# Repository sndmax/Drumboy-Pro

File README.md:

# Drumboy Pro

📖 **[Developer Wiki](https://www.randomwaves.io/drumboy-pro/drumboy-pro-wiki.html)** — full hardware specs, schematics walkthrough, firmware architecture, DSP internals, and memory map.

**An open-source hardware groovebox** — sequencer, sampler, and DSP effects engine built around an STM32H723 (Cortex-M7 @ 550 MHz), with a 540×960 touch-free color display, 42 keys, 8 rotary encoders, and full MIDI/Sync I/O.

This repository holds the complete hardware design (KiCad) and firmware (STM32CubeIDE / C++) for Drumboy Pro, released by [Randomwaves](https://randomwaves.io) as an open hardware/software project.

---

## Overview

The MCU sits at the center of six subsystems: an NT35510 display driven over a 16-bit parallel GPIO bus, 16 MB of external SDRAM for sample streaming, an SGTL5000 audio codec over I2S/I2C, a microSD card for storage, a control surface fanned out over six MCP23017 I/O expanders, and external connectivity (MIDI, Sync, USB-C power).

| | |
|---|---|
| **MCU** | STM32H723ZGT6 — Cortex-M7 @ 550 MHz (VOS0), LQFP-144 |
| **Display** | NT35510, 540×960, 16-bit parallel |
| **SDRAM** | 16 MB (IS42S16800J-7TL-TR), FMC bus |
| **Audio codec** | SGTL5000 — I2S3 audio / I2C3 control |
| **Storage** | microSD (TF-01A), SDMMC2, FAT filesystem |
| **Control surface** | 42 keys, 42 LEDs, 8 rotary encoders — 6× MCP23017 over I2C |
| **Connectivity** | MIDI In/Out, Sync In/Out, USB-C power |
| **Flash** | 1024 KB, split between bootloader and application |

## Features

- **10 sample layers**, each independently modulated by a 10-slot LFO matrix (sample-and-hold at note-trigger time)
- **Per-layer routing** into a shared DSP chain: parametric EQ → 2× multimode filter → 2× send effect → stereo reverb
- **9 effect types** per send slot: Delay, Chorus, Flanger, Phaser, Compressor, Expander, Overdrive, Distortion, Bitcrusher
- **Freeverb/Schroeder-Moorer style reverb** with pre-delay, stereo surround derivation, and nine built-in profiles: Default, Tight, Snap, Chamber, Warehouse, Disco, Dub, Ghost, Texture
- **Sequencer** with 5 song banks per layer, 64 beats per bank, and algorithmic complex-fill generation (timing alignment × level curve templates)
- Hold **Copy** while increasing **Bars** to double the bar count (for example, 2 → 4) and duplicate the entire current song bank across all instruments. Doubling must fit the song-length limit; each bank supports 64 beats and 32 complex fills.
- **MIDI In/Out** (opto-isolated input) and **Sync In/Out** for external clock/gate sync
- **SD-card firmware updates** via a dedicated bootloader with CRC-32 verified staged writes
- Fully open hardware (KiCad) and firmware (C/C++ against the STM32 HAL) — no CMSIS-DSP or external DSP library, all hand-rolled biquad/delay-line DSP on the Cortex-M7 FPU

Choose **Profile** with the second encoder in the Reverb menu or select the field with left/right and change it with up/down. Each profile enables reverb and applies its complete settings through a bypass transition. **Tight** is the starting profile at initialization and for new projects and drumkits. **Default** retains the original settings for an explicit reverb reset and recovery from invalid saved parameters.

| Profile | Intended use | Size | Decay | Damping | PreDelay (ms) | Surround (%) | Dry | Wet |
|---|---|---:|---:|---:|---:|---:|---:|---:|
| Default | Original reset settings | 25 | 50 | 30 | 5 | 25 | 100 | 50 |
| Tight | Techno/house grooves, hats and shakers | 25 | 32 | 65 | 8 | 25 | 100 | 18 |
| Snap | Breakbeat, fast snare/clap and percussion | 10 | 15 | 40 | 10 | 10 | 100 | 18 |
| Chamber | Dark hypnotic percussion, rims and toms | 38 | 55 | 70 | 3 | 30 | 100 | 25 |
| Warehouse | Sparse hits, rides and transitions | 68 | 40 | 60 | 20 | 40 | 100 | 25 |
| Disco | Brighter house/Italo claps, snares and stabs | 40 | 50 | 25 | 20 | 30 | 100 | 30 |
| Dub | Leftfield accents and delay into reverb | 52 | 70 | 75 | 30 | 40 | 100 | 35 |
| Ghost | Wet textures with a shorter tail | 72 | 80 | 70 | 4 | 65 | 0 | 100 |
| Texture | Long atmospheric tails and transitions | 100 | 100 | 65 | 40 | 80 | 0 | 100 |

**Ghost** and **Texture** use Dry 0% / Wet 100% on the shared reverb bus: every source routed into reverb loses its direct signal. For a dedicated texture, route only the intended sources into that bus. Manual edits display **Custom** unless all settings match a built-in profile; the global Size encoder assignment remains available. Projects and drumkits keep the existing file format and restore the profile name from the saved settings. Older Room, Hall, Dark and Ambient settings load as Custom with their parameters preserved.

## Repository structure

```
01 Hardware/
  Main/       KiCad project — main board (Drumboy_Main)
  Top/        KiCad project — top/control-surface board (Drumboy_Top)
  Drawing/    Mechanical drawings, enclosure models, graphics, fonts

02 Software/
  Drumboy-Pro-Boot-H723/   Bootloader — STM32CubeIDE project (own repo, linked below)
  Drumboy-Pro-App-H723/    Application firmware — STM32CubeIDE project (own repo, linked below)
  Firmware/                 Prebuilt firmware binaries
  Sd Card/                  Reference SD card contents (samples, presets, drumkits, system data)
```

### Related repositories

Firmware is split into two independently-built projects that share one flash device — a bad application build can never brick the update path:

| Project | Responsibility |
|---|---|
| [Drumboy-Pro-Boot-H723](https://github.com/Randomwaves-Team/Drumboy-Pro-Boot-H723) | Checks the SD card for a firmware package, validates and programs it, then jumps to the application |
| [Drumboy-Pro-App-H723](https://github.com/Randomwaves-Team/Drumboy-Pro-App-H723) | The sequencer, DSP engine, UI, and all runtime behavior |

## Hardware

Designed in **KiCad 7**. Open `01 Hardware/Main/Drumboy_Main.kicad_pro` for the main board, or `01 Hardware/Top/Drumboy_Top.kicad_pro` for the control-surface board. All third-party symbols, footprints, and 3D models are vendored under each project's `Library/` folder.

Mechanical design (enclosure and 3D model) lives in `01 Hardware/Drawing/` as **Rhinoceros 8** files — `Drumboy Pro 2D.3dm` and `Drumboy Pro 3D.zip` (zipped to keep it under GitHub's file size limit; unzip to get the `.3dm`).

A full BOM is generated from KiCad at `production/bom.csv`. See the [wiki](https://www.randomwaves.io/drumboy-pro/drumboy-pro-wiki.html) for the annotated schematic walkthrough, clock tree, power-domain isolation scheme, and key component reference.

## Firmware

Built with **STM32CubeIDE**, written in C/C++ against the STM32 HAL.

- Bootloader owns flash sector 0 (`0x08000000`–`0x0801FFFF`)
- Application owns sectors 1–7 (`0x08020000`–`0x080FFFFF`), with the vector table relocated at startup

To flash over SWD, wire an ST-Link V2 to the board's `SWDIO` (PA13), `SWCLK` (PA14), and `GND` pins, then build and flash from STM32CubeIDE. See the wiki's [Build, Flash & Debug](https://www.randomwaves.io/drumboy-pro/drumboy-pro-wiki.html) section for details.

## License

Released under the [MIT License](LICENSE).

## Community

- 💬 [Discord community](https://discord.gg/5atevNH6UU) — join the discussion
- 🌐 [randomwaves.io](https://www.randomwaves.io)
- ✉️ [hello@randomwaves.io](mailto:hello@randomwaves.io)

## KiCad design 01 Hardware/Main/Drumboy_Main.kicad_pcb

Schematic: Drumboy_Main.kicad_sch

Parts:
C1, C2, C3, C4, C5, C6, C7, C8, C9, C10, C11, C12, C16, C20, C23, C26, C28, C30, C32, C33, C34, C35, C36, C37, C38, C41, C42, C44, C45, C47, C49, C51, C53, C55, C57, C59, C61, C63, C65, C67, C68, C71: 0.1uF; C_0603_1608Metric
C13, C17, C27, C29, C31, C39, C48, C50, C52, C54, C56, C58, C72: 4.7uF; C_0603_1608Metric
C14, C18, C60, C62, C64, C66: 2.2uF; C_0603_1608Metric
C15, C19: 33pF; C_0603_1608Metric
C21, C24, C40, C69, C70, C73, C75: 1uF; C_0603_1608Metric
C22, C25, C43, C46: 10uF; C_0603_1608Metric
C77, C78, C79, C80, C81, C82, C83, C84, C85, C86, C87, C88, C89, C90, C91, C92: 0.01uF; C_0603_1608Metric
D1, D2, D3, D4, D39, D40, D41, D42, D43, D44: LED G; LED_0402_1005Metric; LCSC Part # C130722
D5, D6, D30, D31, D33, D34, D36, D37: LED Y; LED_0402_1005Metric; LCSC Part # C130721
D7, D8, D21, D22, D24, D25, D27, D28: LED O; LED_0402_1005Metric; LCSC Part # C130720
D9: MBR0520LT3G; SOD3716X135N; Mouser Part Number 863-MBR0520LT3G
D10: 1N4148WT; D_SOD-523; LCSC Part # C27748
D11, D14, D17, D20, D23, D26, D29, D32, D35, D38: LED W; LED_0603_1608Metric; LCSC Part # C158100
D12, D13, D15, D16, D18, D19: LED R; LED_0402_1005Metric; LCSC Part # C130719
F1: MF-PSMF075X-2; Fuse_0805_2012Metric; LCSC Part # C116173
FB1, FB2: BLM18AG102SN1D; L_0603_1608Metric; LCSC Part # C85824
FB3, FB4, FB5, FB6, FB7, FB8, FB9: BLM18AG601SN1D; L_0603_1608Metric; LCSC Part # C19330
IC1: IS42S16800J-7TL-TR; SOP80P1176X120-54N; Manufacturer_Part_Number IS42S16400J-7TL-TR; Mouser Part Number 870-IS42S16400J7TLTR
IC2: STM32H723ZGT6; QFP50P2200X2200X160-144N; Mouser Part Number 511-STM32H723ZGT6
IC3: MP3302DJ-LF-Z; SOT95P280X100-5N; Mouser Part Number 946-MP3302DJLFZ
IC4, IC5: AP2112K-3.3TRG1; SOT95P285X140-5N; Mouser Part Number 621-AP2112K-3.3TRG1
IC6: AP2112K-1.8TRG1; SOT95P285X140-5N; Mouser Part Number 621-AP2112K-1.8TRG1
IC7: SGTL5000XNBA3R2; QFN50P500X500X90-33N; Manufacturer_Part_Number SGTL5000XNBA3R2; Mouser Part Number 771-SGTL5000XNBA3R2
J1: TYPE-C-31-M-17; TYPEC31M17; LCSC Part # C283540
J2: FH26W-51S-0.3SHW_60_; HIROSE_FH26W-51S-0.3SHW_60_; PARTREV DRW NO: EDC3-323714-05; LCSC Part # C424656
J3: M20-8890345; M208890345; Mouser Part Number 855-M20-8890345
J4, J5, J6, J7, J8, J9, J10: SJ1-3515-SMT-TR; SJ13515SMTTR; Mouser Part Number 490-SJ1-3515-SMT-TR
L1: NRS5024T4R7MMGJ; Mouser Part Number 963-NRS5024T4R7MMGJ
MICRO_SD1: TF-01A; LCSC Part # C91145
R1, R2: 5.1K; R_0603_1608Metric
R3, R55, R59, R63, R66, R69, R72, R75, R78, R89, R92: 3.3K; R_0603_1608Metric
R4, R10, R12, R16, R23, R24, R25, R26, R28, R29, R32, R36, R37, R38, R39, R40, R41, R42, R43, R44, R45, R46, R47, R81, R82, R83, R84, R85, R86, R87, R88, R99, R100, R101, R102, R103, R104, R105, R106, R107, R108, R109, R110, R111, R112, R113, R114, R115, R116, R117, R118, R119, R120, R121, R122: 10K; R_0603_1608Metric
R5: 4.7; R_0603_1608Metric
R6, R8, R9, R11, R14, R17, R20, R56, R57, R60, R61, R64, R65, R67, R68, R70, R71, R73, R74, R76, R77, R79, R80, R90, R91, R93, R94, R95, R96, R97, R98: 2.2K; R_0603_1608Metric
R7, R13: 100K; R_0603_1608Metric
R15, R18, R19, R21, R22: 47K; R_0603_1608Metric
R27: 10; R_0603_1608Metric
R30, R31, R48: 220; R_0603_1608Metric
R33, R34, R35, R50, R51, R52, R54: 0; R_0603_1608Metric
R49: 100; R_0603_1608Metric
R53: 470; R_0603_1608Metric
R58, R62: 47; R_0603_1608Metric
S1: SC12P-AQR; SC12PAQR; Manufacturer_Part_Number SC12P-AQR; Mouser Part Number 113-SC12PAQR
S2, S3: 431481031816; PART-NUMBER 431481031816
SW1, SW2, SW3, SW4, SW5, SW6, SW7, SW8, SW9, SW10, SW11, SW12, SW13, SW14, SW15, SW16, SW17, SW18, SW19, SW20, SW21, SW22, SW23, SW24, SW25, SW26, SW27, SW28, SW29, SW30, SW31, SW32, SW33, SW34, SW35, SW36, SW37, SW38, SW39, SW40, SW41, SW42: SW_Push; SW_PG1350; LCSC Part # C400229
U1, U2, U3, U4, U5, U6: MCP23017_ML; QFN65P600X600X100-29N-D; LCSC Part # C629439
U7: H11L1; SMDIP-6_W9.53mm; LCSC Part # C78589
U8, U9, U10, U11, U12, U13, U14, U15: PEC12R-4017F-N0024; PEC12R4017FN0024; Mouser Part Number 652-PEC12R-4017F-N24
Y1: ABM7-8MHZ-D2Y-T; ABM7; Mouser Part Number 815-ABM7-8-D2Y-T

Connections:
+1.8V_DAC: C65.1, C66.1, IC6.5 (VOUT), IC7.30 (VDDD)
+3.3V_DAC: C61.1, C62.1, FB9.1, IC5.5 (VOUT), IC6.1 (VIN), IC6.3 (EN), IC7.20 (VDDIO)
+3.3V_DAC_ANA: C63.1, C64.1, FB9.2, IC7.5 (VDDA)
+3.3V_DIG: C1.1, C2.1, C3.1, C4.1, C5.1, C6.1, C7.1, C8.1, C9.1, C10.1, C11.1, C12.1, C13.1, C16.1, C17.1, C26.1, C27.1, C32.1, C33.1, C34.1, C35.1, C36.1, C37.1, C38.1, C39.1, C43.1, C44.1, C47.1, C48.1, C49.1, C50.1, C51.1, C52.1, C53.1, C54.1, C55.1, C56.1, C57.1, C58.1, C71.1, C72.1, IC1.1 (VDD_1), IC1.3 (VDDQ_1), IC1.9 (VDDQ_2), IC1.14 (VDD_2), IC1.27 (VDD_3), IC1.43 (VDDQ_3), IC1.49 (VDDQ_4), IC2.6 (VBAT), IC2.17 (VDD_1), IC2.30 (VDD_2), IC2.32 (VREF+), IC2.33 (VDDA), IC2.39 (VDD_3), IC2.52 (VDD_4), IC2.62 (VDD_5), IC2.72 (VDD_6), IC2.84 (VDD_7), IC2.95 (VDD33USB), IC2.108 (VDD_8), IC2.121 (VDD_9), IC2.131 (VDD_10), IC2.144 (VDD_11), IC4.5 (VOUT), J2.2, J2.3, MICRO_SD1.4 (VDD), R6.1, R12.2, R15.2, R18.2, R19.2, R21.2, R22.2, R23.2, R24.2, R25.2, R26.2, R28.2, R29.2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; also elsewhere on the board
+5V: C23.1, C24.1, C25.1, FB3.1, FB5.1, FB7.1, S1.C1 (C1_NO)
+5V_BUS: C20.1, C21.1, C22.1, FB1.2, S1.B1 (B1_COM)
+5V_DAC: C59.1, C60.1, FB7.2, IC5.1 (VIN), IC5.3 (EN)
+5V_DIG: C45.1, C46.1, FB3.2, IC4.1 (VIN), R3.1, R32.1
+5V_LCD: C28.1, C29.1, FB5.2, L1.1, R27.1
+5V_USB: F1.1, J1.A9 (VBUS_1), J1.B9 (VBUS_2)
BL_EN: IC3.4 (EN), R4.2, R7.2
BL_GND: IC3.3 (FB), J2.45, J2.46, J2.47, J2.48, J2.49, R5.1
BL_IN: C40.1, IC3.5 (IN), R27.2
BL_SW: D9.2 (A), IC3.1 (SW), L1.2
BL_VCC: C30.1, C31.1, D9.1 (K), J2.50, J2.51
BOOT0: IC2.138 (BOOT0), R16.1
BUTTON: IC2.22 (PF10), R31.2
ENCO_0A: C77.1, IC2.1 (PE2), R85.2
ENCO_0B: C78.1, IC2.5 (PE6), R86.2
ENCO_1A: C81.1, IC2.2 (PE3), R103.2
ENCO_1B: C82.1, IC2.41 (PA5), R104.2
ENCO_2A: C85.1, IC2.3 (PE4), R111.2
ENCO_2B: C86.1, IC2.42 (PA6), R112.2
ENCO_3A: C89.1, IC2.4 (PE5), R119.2
ENCO_3B: C90.1, IC2.43 (PA7), R120.2
ENCO_4A: C79.1, IC2.91 (PG6), R87.2
ENCO_4B: C80.1, IC2.87 (PG2), R88.2
ENCO_5A: C83.1, IC2.92 (PG7), R105.2
ENCO_5B: C84.1, IC2.88 (PG3), R106.2
ENCO_6A: C87.1, IC2.20 (PF8), R113.2
ENCO_6B: C88.1, IC2.8 (PC14-OSC32_IN), R114.2
ENCO_7A: C91.1, IC2.21 (PF9), R121.2
ENCO_7B: C92.1, IC2.9 (PC15-OSC32_OUT), R122.2
FMC_A0: IC1.23 (A0), IC2.10 (PF0)
FMC_A1: IC1.24 (A1), IC2.11 (PF1)
FMC_A2: IC1.25 (A2), IC2.12 (PF2)
FMC_A3: IC1.26 (A3), IC2.13 (PF3)
FMC_A4: IC1.29 (A4), IC2.14 (PF4)
FMC_A5: IC1.30 (A5), IC2.15 (PF5)
FMC_A6: IC1.31 (A6), IC2.50 (PF12)
FMC_A7: IC1.32 (A7), IC2.53 (PF13)
FMC_A8: IC1.33 (A8), IC2.54 (PF14)
FMC_A9: IC1.34 (A9), IC2.55 (PF15)
FMC_A10: IC1.22 (A10), IC2.56 (PG0)
FMC_A11: IC1.35 (A11), IC2.57 (PG1)
FMC_BA0: IC1.20 (BA0), IC2.89 (PG4)
FMC_BA1: IC1.21 (BA1), IC2.90 (PG5)
FMC_D0: IC1.2 (DQ0), IC2.85 (PD14)
FMC_D1: IC1.4 (DQ1), IC2.86 (PD15)
FMC_D2: IC1.5 (DQ2), IC2.114 (PD0)
FMC_D3: IC1.7 (DQ3), IC2.115 (PD1)
FMC_D4: IC1.8 (DQ4), IC2.58 (PE7)
FMC_D5: IC1.10 (DQ5), IC2.59 (PE8)
FMC_D6: IC1.11 (DQ6), IC2.60 (PE9)
FMC_D7: IC1.13 (DQ7), IC2.63 (PE10)
FMC_D8: IC1.42 (DQ8), IC2.64 (PE11)
FMC_D9: IC1.44 (DQ9), IC2.65 (PE12)
FMC_D10: IC1.45 (DQ10), IC2.66 (PE13)
FMC_D11: IC1.47 (DQ11), IC2.67 (PE14)
FMC_D12: IC1.48 (DQ12), IC2.68 (PE15)
FMC_D13: IC1.50 (DQ13), IC2.77 (PD8)
FMC_D14: IC1.51 (DQ14), IC2.78 (PD9)
FMC_D15: IC1.53 (DQ15), IC2.79 (PD10)
FMC_NBL0: IC1.15 (LDQM), IC2.141 (PE0)
FMC_NBL1: IC1.39 (UDQM), IC2.142 (PE1)
FMC_SDCKE0: IC1.37 (CKE), IC2.45 (PC5)
FMC_SDCLK: IC1.38 (CLK), IC2.93 (PG8)
FMC_SDNCAS: IC1.17 (~CAS), IC2.132 (PG15)
FMC_SDNE0: IC1.19 (~CS), IC2.44 (PC4)
FMC_SDNRAS: IC1.18 (~RAS), IC2.49 (PF11)
FMC_SDNWE: IC1.16 (~WE), IC2.26 (PC0)
GND: C20.2, C21.2, C22.2, C23.2, C24.2, C25.2, D1.1 (K), D2.1 (K), D3.1 (K), D4.1 (K), D5.1 (K), D6.1 (K), D7.1 (K), D8.1 (K), FB2.2, FB4.1, FB6.1, FB8.1, J3.2
GND_DAC: C59.2, C60.2, C61.2, C62.2, C63.2, C64.2, C65.2, C66.2, C67.2, C68.2, FB8.2, IC5.2 (GND), IC6.2 (GND), IC7.1 (GND_1), IC7.3 (GND_2), IC7.7 (AGND), IC7.31 (CTRL_ADR0_CS), IC7.32 (CTRL_MODE), IC7.33 (GND_3), J9.1 (SLEEVE), J10.1 (SLEEVE)
GND_DIG: C1.2, C2.2, C3.2, C4.2, C5.2, C6.2, C7.2, C8.2, C9.2, C10.2, C11.2, C12.2, C13.2, C14.2, C15.2, C16.2, C17.2, C18.2, C19.2, C26.2, C27.2, C32.2, C33.2, C34.2, C35.2, C36.2, C37.2, C38.2, C39.2, C41.2, C42.2, C43.2, C44.2, C45.2, C46.2, C47.2, C48.2, C49.2, C50.2, C51.2, C52.2, C53.2, C54.2, C55.2, C56.2, C57.2, C58.2, C71.2, C72.2, C77.2, C78.2, C79.2, C80.2, C81.2, C82.2, C83.2, C84.2, C85.2, C86.2, C87.2, C88.2, C89.2, C90.2, C91.2, C92.2, D11.1 (K), D12.1 (K), D13.1 (K), D14.1 (K), D15.1 (K), D16.1 (K), D17.1 (K), D18.1 (K), D19.1 (K), D20.1 (K), D21.1 (K), D22.1 (K), D23.1 (K), D24.1 (K), D25.1 (K)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; also elsewhere on the board
GND_LCD: C28.2, C29.2, C30.2, C31.2, C40.2, FB6.2, IC3.2 (GND), R5.2, R7.1, R13.1
GND_USB: FB2.1, J1.A12 (GND_1), J1.B12 (GND_2), R1.2, R2.2
HPHONE_L: IC7.6 (HP_L), R50.1
HPHONE_R: IC7.2 (HP_R), R52.1
HPHONE_VGND: IC7.4 (HP_VGND), J8.1 (SLEEVE)
HP_L: J8.2 (TIP), R50.2
HP_R: J8.3 (RING), R52.2
I2C3_SCL: IC2.100 (PA8), IC7.29 (CTRL_CLK), R23.1, U1.8 (SCK), U2.8 (SCK), U3.8 (SCK)
I2C3_SDA: IC2.99 (PC9), IC7.27 (CTRL_DATA), R25.1, U1.9 (SDA), U2.9 (SDA), U3.9 (SDA)
I2C4_SCL: IC2.81 (PD12), R24.1, U4.8 (SCK), U5.8 (SCK), U6.8 (SCK)
I2C4_SDA: IC2.82 (PD13), R26.1, U4.9 (SDA), U5.9 (SDA), U6.9 (SDA)
I2S3_CK: IC2.111 (PC10), IC7.24 (I2S_SCLK)
I2S3_MCK: IC2.97 (PC7), R49.1
I2S3_MCK_IN: IC7.21 (SYS_MCLK), R49.2
I2S3_SDI: IC2.112 (PC11), IC7.25 (I2S_DOUT)
I2S3_SDO: IC2.113 (PC12), IC7.26 (I2S_DIN)
I2S3_WS: IC2.40 (PA4), IC7.23 (I2S_LRCLK)
LCD_BL: IC2.129 (PG14), R4.1, R10.1
LCD_CS: IC2.116 (PD2), J2.9
LCD_D0: IC2.46 (PB0), J2.15
LCD_D1: IC2.47 (PB1), J2.16
LCD_D2: IC2.48 (PB2), J2.17
LCD_D3: IC2.133 (PB3), J2.18
LCD_D4: IC2.134 (PB4), J2.19
LCD_D5: IC2.135 (PB5), J2.20
LCD_D6: IC2.136 (PB6), J2.21
LCD_D7: IC2.137 (PB7), J2.22
LCD_D8: IC2.139 (PB8), J2.23
LCD_D9: IC2.140 (PB9), J2.24
LCD_D10: IC2.69 (PB10), J2.25
LCD_D11: IC2.70 (PB11), J2.26
LCD_D12: IC2.73 (PB12), J2.27
LCD_D13: IC2.74 (PB13), J2.28
LCD_D14: IC2.75 (PB14), J2.29
LCD_D15: IC2.76 (PB15), J2.30
LCD_IM0: J2.4, R33.1
LCD_IM1: J2.5, R34.1
LCD_IM2: J2.6, R35.1
LCD_PWM: J2.44, R10.2, R13.2
LCD_RD: IC2.117 (PD3), J2.12
LCD_RESET: IC2.128 (PG13), J2.13
LCD_RS: IC2.119 (PD5), J2.10
LCD_WR: IC2.118 (PD4), J2.11
LED0: IC2.27 (PC1), R8.2, R9.2
LED1: IC2.28 (PC2_C), R11.2, R14.2
LED2: IC2.29 (PC3_C), R17.2, R20.2
LED_EQ_A_00: R97.1, U5.17 (GPA0)
LED_EQ_A_01: R95.1, U5.18 (GPA1)
LED_EQ_A_02: R93.1, U5.19 (GPA2)
LED_EQ_A_03: R90.1, U5.20 (GPA3)
LED_EQ_A_04: R79.1, U5.21 (GPA4)
LED_EQ_A_05: R76.1, U5.22 (GPA5)
LED_EQ_A_06: R73.1, U5.23 (GPA6)
LED_EQ_A_07: R70.1, U5.24 (GPA7)
LED_EQ_A_08: R67.1, U5.25 (GPB0)
LED_EQ_A_09: R64.1, U5.26 (GPB1)
LED_EQ_A_10: R60.1, U5.27 (GPB2)
LED_EQ_A_11: R56.1, U5.28 (GPB3)
LED_EQ_B_00: R98.1, U6.17 (GPA0)
LED_EQ_B_01: R96.1, U6.18 (GPA1)
LED_EQ_B_02: R94.1, U6.19 (GPA2)
LED_EQ_B_03: R91.1, U6.20 (GPA3)
LED_EQ_B_04: R80.1, U6.21 (GPA4)
LED_EQ_B_05: R77.1, U6.22 (GPA5)
LED_EQ_B_06: R74.1, U6.23 (GPA6)
LED_EQ_B_07: R71.1, U6.24 (GPA7)
LED_EQ_B_08: R68.1, U6.25 (GPB0)
LED_EQ_B_09: R65.1, U6.26 (GPB1)
LED_EQ_B_10: R61.1, U6.27 (GPB2)
LED_EQ_B_11: R57.1, U6.28 (GPB3)
LED_KEY_00: R55.1, U4.17 (GPA0)
LED_KEY_01: R59.1, U4.18 (GPA1)
LED_KEY_02: R63.1, U4.19 (GPA2)
LED_KEY_03: R66.1, U4.20 (GPA3)
LED_KEY_04: R69.1, U4.21 (GPA4)
LED_KEY_05: R72.1, U4.22 (GPA5)
LED_KEY_06: R75.1, U4.23 (GPA6)
LED_KEY_07: R78.1, U4.24 (GPA7)
LED_KEY_08: R89.1, U4.25 (GPB0)
LED_KEY_09: R92.1, U4.26 (GPB1)
LINEIN_L: C69.1, IC7.14 (LINEIN_L)
LINEIN_R: C70.1, IC7.13 (LINEIN_R)
LINEOUT_L: C73.1, IC7.12 (LINEOUT_L)
LINEOUT_R: C75.1, IC7.11 (LINEOUT_R)
LI_L: C69.2, J9.2 (TIP)
LI_R: C70.2, J9.3 (RING)
LO_L: C73.2, J10.2 (TIP)
LO_R: C75.2, J10.3 (RING)
MIC: C68.1, IC7.15 (MIC)
MIDI_RX: IC2.101 (PA9), R53.1, U7.4
MIDI_RX_A: D10.1 (K), R48.1, U7.1
MIDI_RX_C: D10.2 (A), J6.2 (TIP), U7.2
MIDI_RX_GND: J6.1 (SLEEVE), R51.2
MIDI_RX_SOURCE: J6.3 (RING), R48.2
MIDI_TX: IC2.96 (PC6), R58.1
MIDI_TX_GND: J7.1 (SLEEVE), R54.2
MIDI_TX_SINK: J7.2 (TIP), R58.2
MIDI_TX_SOURCE: J7.3 (RING), R62.2
MX_A_INT: IC2.34 (PA0), R37.1, U2.16 (INTA)
MX_A_RESET: R43.1, U2.14 (~RESET)
MX_B_INT: IC2.35 (PA1), R38.1, U3.16 (INTA)
MX_B_RESET: R44.1, U3.14 (~RESET)
MX_C_INT: R39.1, U4.16 (INTA)
MX_C_RESET: R45.1, U4.14 (~RESET)
MX_D_INT: R40.1, U5.16 (INTA)
MX_D_RESET: R46.1, U5.14 (~RESET)
MX_E_INT: R41.1, U6.16 (INTA)
MX_E_RESET: R47.1, U6.14 (~RESET)
MX_X_INT: IC2.80 (PD11), R36.1, U1.16 (INTA)
MX_X_RESET: R42.1, U1.14 (~RESET)
NRST: IC2.25 (NRST), R30.2
unnamed: C41.1, R28.1, R30.1, S2.3, S2.4
unnamed: C42.1, R29.1, R31.1, S3.3, S3.4
unnamed: D1.2 (A), R3.2
unnamed: D2.2 (A), R6.2
unnamed: D3.2 (A), R8.1
unnamed: D4.2 (A), R9.1
unnamed: D5.2 (A), R11.1
unnamed: D6.2 (A), R14.1
unnamed: D7.2 (A), R17.1
unnamed: D8.2 (A), R20.1
unnamed: D11.2 (A), R55.2
unnamed: D12.2 (A), R56.2
unnamed: D13.2 (A), R57.2
unnamed: D14.2 (A), R59.2
unnamed: D15.2 (A), R60.2
unnamed: D16.2 (A), R61.2
unnamed: D17.2 (A), R63.2
unnamed: D18.2 (A), R64.2
unnamed: D19.2 (A), R65.2
unnamed: D20.2 (A), R66.2
unnamed: D21.2 (A), R67.2
unnamed: D22.2 (A), R68.2
unnamed: D23.2 (A), R69.2
unnamed: D24.2 (A), R70.2
unnamed: D25.2 (A), R71.2
unnamed: D26.2 (A), R72.2
unnamed: D27.2 (A), R73.2
unnamed: D28.2 (A), R74.2
unnamed: D29.2 (A), R75.2
unnamed: D30.2 (A), R76.2
unnamed: D31.2 (A), R77.2
unnamed: D32.2 (A), R78.2
unnamed: D33.2 (A), R79.2
unnamed: D34.2 (A), R80.2
unnamed: D35.2 (A), R89.2
unnamed: D36.2 (A), R90.2
unnamed: D37.2 (A), R91.2
unnamed: D38.2 (A), R92.2
unnamed: D39.2 (A), R93.2
unnamed: D40.2 (A), R94.2
unnamed: D41.2 (A), R95.2
unnamed: D42.2 (A), R96.2
unnamed: D43.2 (A), R97.2
unnamed: D44.2 (A), R98.2
unnamed: F1.2, FB1.1
unnamed: IC4.3 (EN), R32.2
PDR_ON: IC2.143 (PDR_ON), R12.1
PH0: C15.1, IC2.23 (PH0-OSC_IN), Y1.1
PH1: C19.1, IC2.24 (PH1-OSC_OUT), Y1.2
ROT_0A: R81.1, R85.1, U8.A1 (CHANNEL_A)
ROT_0B: R82.1, R86.1, U8.B1 (CHANNEL_B)
ROT_1A: R99.1, R103.1, U10.A1 (CHANNEL_A)
ROT_1B: R100.1, R104.1, U10.B1 (CHANNEL_B)
ROT_2A: R107.1, R111.1, U12.A1 (CHANNEL_A)
ROT_2B: R108.1, R112.1, U12.B1 (CHANNEL_B)
ROT_3A: R115.1, R119.1, U14.A1 (CHANNEL_A)
ROT_3B: R116.1, R120.1, U14.B1 (CHANNEL_B)
ROT_4A: R83.1, R87.1, U9.A1 (CHANNEL_A)
ROT_4B: R84.1, R88.1, U9.B1 (CHANNEL_B)
ROT_5A: R101.1, R105.1, U11.A1 (CHANNEL_A)
ROT_5B: R102.1, R106.1, U11.B1 (CHANNEL_B)
ROT_6A: R109.1, R113.1, U13.A1 (CHANNEL_A)
ROT_6B: R110.1, R114.1, U13.B1 (CHANNEL_B)
ROT_7A: R117.1, R121.1, U15.A1 (CHANNEL_A)
ROT_7B: R118.1, R122.1, U15.B1 (CHANNEL_B)
SDMMC2_CK: IC2.122 (PD6), MICRO_SD1.5 (CLK); also elsewhere on the board
SDMMC2_CMD: IC2.123 (PD7), MICRO_SD1.3 (CMD), R22.1; also elsewhere on the board
SDMMC2_D0: IC2.124 (PG9), MICRO_SD1.7 (DAT0), R15.1; also elsewhere on the board
SDMMC2_D1: IC2.125 (PG10), MICRO_SD1.8 (DAT1), R18.1; also elsewhere on the board
SDMMC2_D2: IC2.126 (PG11), MICRO_SD1.1 (DAT2), R19.1; also elsewhere on the board
SDMMC2_D3: IC2.127 (PG12), MICRO_SD1.2 (CD/DAT3), R21.1; also elsewhere on the board
SDMMC2_DETECT: IC2.7 (PC13), MICRO_SD1.CD1 (CD); also elsewhere on the board
SWCLK: IC2.109 (PA14), J3.3
SWDIO: IC2.105 (PA13), J3.1
SW_A_00: SW1.1, U2.17 (GPA0)
SW_A_01: SW4.1, U2.18 (GPA1)
SW_A_02: SW7.1, U2.19 (GPA2)
SW_A_03: SW10.1, U2.20 (GPA3)
SW_A_04: SW13.1, U2.21 (GPA4)
SW_A_05: SW16.1, U2.22 (GPA5)
SW_A_06: SW19.1, U2.23 (GPA6)
SW_A_07: SW22.1, U2.24 (GPA7)
SW_A_08: SW25.1, U2.25 (GPB0)
SW_A_09: SW28.1, U2.26 (GPB1)
SW_A_10: SW31.1, U2.27 (GPB2)
SW_A_11: SW33.1, U2.28 (GPB3)
SW_A_12: SW35.1, U2.1 (GPB4)
SW_A_13: SW37.1, U2.2 (GPB5)
SW_A_14: SW39.1, U2.3 (GPB6)
SW_A_15: SW41.1, U2.4 (GPB7)
SW_B_00: SW2.1, U3.17 (GPA0)
SW_B_01: SW5.1, U3.18 (GPA1)
SW_B_02: SW8.1, U3.19 (GPA2)
SW_B_03: SW11.1, U3.20 (GPA3)
SW_B_04: SW14.1, U3.21 (GPA4)
SW_B_05: SW17.1, U3.22 (GPA5)
SW_B_06: SW20.1, U3.23 (GPA6)
SW_B_07: SW23.1, U3.24 (GPA7)
SW_B_08: SW26.1, U3.25 (GPB0)
SW_B_09: SW29.1, U3.26 (GPB1)
SW_B_10: SW32.1, U3.27 (GPB2)
SW_B_11: SW34.1, U3.28 (GPB3)
SW_B_12: SW36.1, U3.1 (GPB4)
SW_B_13: SW38.1, U3.2 (GPB5)
SW_B_14: SW40.1, U3.3 (GPB6)
SW_B_15: SW42.1, U3.4 (GPB7)
SW_X_00: SW3.1, U1.17 (GPA0)
SW_X_01: SW6.1, U1.18 (GPA1)
SW_X_02: SW9.1, U1.19 (GPA2)
SW_X_03: SW12.1, U1.20 (GPA3)
SW_X_04: SW15.1, U1.21 (GPA4)
SW_X_05: SW18.1, U1.22 (GPA5)
SW_X_06: SW21.1, U1.23 (GPA6)
SW_X_07: SW24.1, U1.24 (GPA7)
SW_X_08: SW27.1, U1.25 (GPB0)
SW_X_09: SW30.1, U1.26 (GPB1)
SYNC_IN: IC2.110 (PA15), J4.2 (TIP)
SYNC_IN_RX: IC2.18 (PF6), J4.3 (RING)
SYNC_IN_TX: IC2.19 (PF7), J4.1 (SLEEVE)
SYNC_OUT: IC2.102 (PA10), J5.2 (TIP)
SYNC_OUT_RX: IC2.103 (PA11), J5.1 (SLEEVE)
SYNC_OUT_TX: IC2.104 (PA12), J5.3 (RING)
USB_CC1: J1.A5 (CC1), R1.1
USB_CC2: J1.B5 (CC2), R2.1
VAG: C67.1, IC7.10 (VAG)
VCAP_1: C14.1, IC2.71 (VCAP_1)
VCAP_2: C18.1, IC2.106 (VCAP_2)

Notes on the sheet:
C130721
DAC
Encoder
VolReg Dig
SDMMC
LED 0402 RED
LED Layer
I2C Address: 0x23
C130719
I2C Address: 0x24
C400229
LED 0402 ORANGE
PG1350 Kaihl Red
LCD
CPU
C130725
STM32
CORE
C130722
LED 0402 YGREEN
Drumboy Pro
I/O Expander
EXT Interrupts 00 A00 SwitchA 01 A01 SwitchB 02 E02 Encoder0 03 E03 Encoder1 04 E04 Encoder2 05 E05 Encoder3 06 G06 Encoder4 07 G07 Encoder5 08 F08 Encoder6 09 F09 Encoder7 10 F10 Button 11 D11 SwitchX 12 --- 13 --- 14 --- 15 A15 SyncIn
I2C Address: 0x21
DIG
I2C Address: 0x14
Sync / Midi
Switch L
SDRAM
LED 0402 YELLOW
USB C
USB
PG1350 Kaihl Black
200mV 40mA
I2C Address: 0x25
Switch R
LED 0402 WHITE
LED Right-EQ
C130720
I2C Address: 0x20

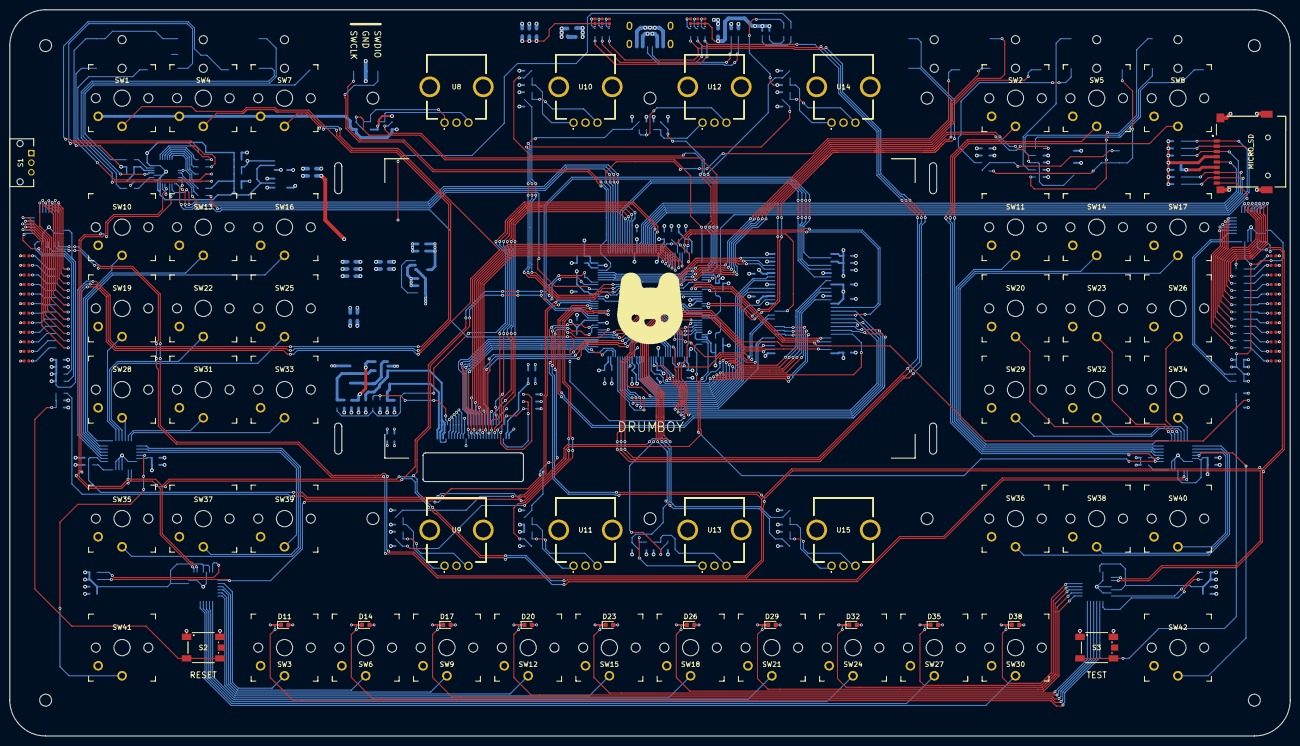
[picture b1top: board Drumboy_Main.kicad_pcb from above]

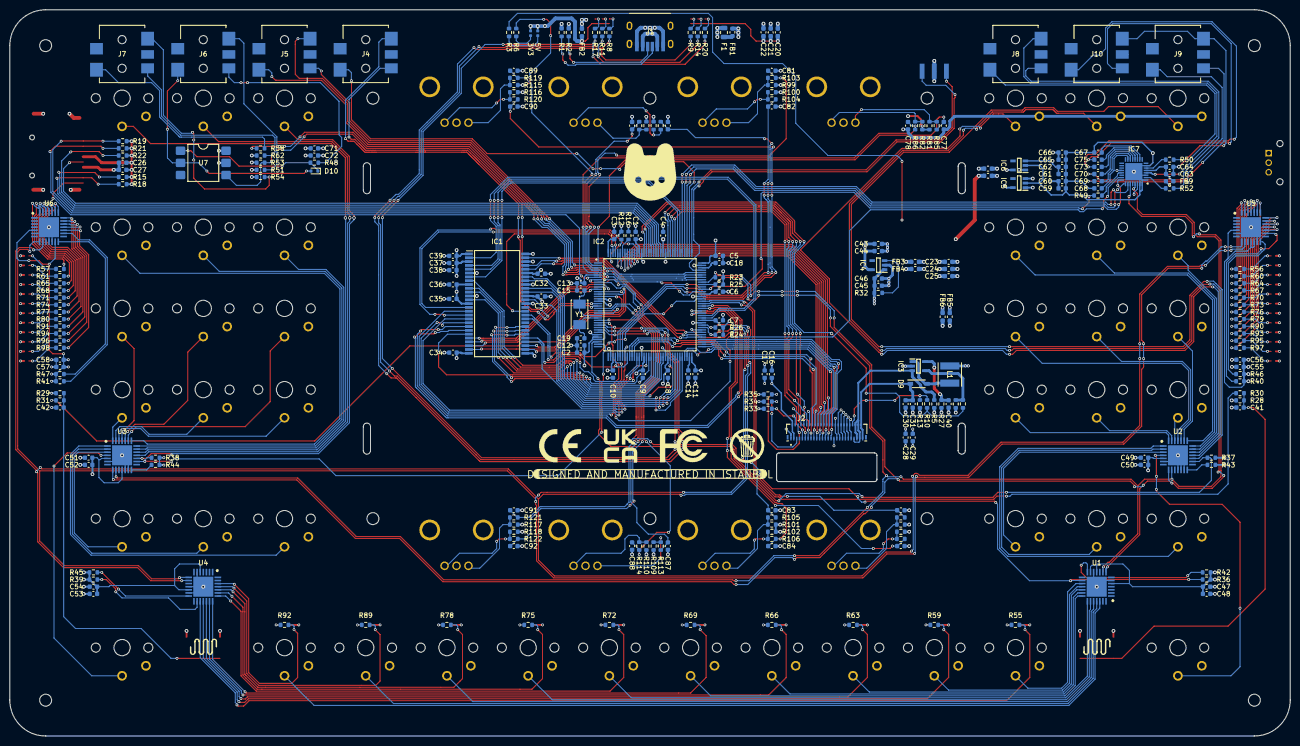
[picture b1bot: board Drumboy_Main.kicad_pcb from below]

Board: 4 copper layers, 268.0 x 152.0 mm, 346 parts (252 on the bottom side), 312 nets.

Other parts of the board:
MICRO_SD: TF-01A

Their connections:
+3.3V_DIG: MICRO_SD.4 (VDD); also elsewhere on the board
GND_DIG: MICRO_SD.6 (VSS), MICRO_SD.MP1 (SHIELD), MICRO_SD.MP2 (SHIELD), MICRO_SD.MP3 (SHIELD), MICRO_SD.MP4 (SHIELD); also elsewhere on the board
SDMMC2_CK: MICRO_SD.5 (CLK); also elsewhere on the board
SDMMC2_CMD: MICRO_SD.3 (CMD); also elsewhere on the board
SDMMC2_D0: MICRO_SD.7 (DAT0); also elsewhere on the board
SDMMC2_D1: MICRO_SD.8 (DAT1); also elsewhere on the board
SDMMC2_D2: MICRO_SD.1 (DAT2); also elsewhere on the board
SDMMC2_D3: MICRO_SD.2 (CD/DAT3); also elsewhere on the board
SDMMC2_DETECT: MICRO_SD.CD1 (CD); also elsewhere on the board

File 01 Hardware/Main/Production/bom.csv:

Designator;Footprint;Quantity;Value;LCSC Part #
C1, C10, C11, C12, C16, C2, C20, C23, C26, C28, C3, C30, C32, C33, C34, C35, C36, C37, C38, C4, C41, C42, C44, C45, C47, C49, C5, C51, C53, C55, C57, C59, C6, C61, C63, C65, C67, C68, C7, C71, C8, C9;603;42;0.1uF;
C13, C17, C27, C29, C31, C39, C48, C50, C52, C54, C56, C58, C72;603;13;4.7uF;
C14, C18, C60, C62, C64, C66;603;6;2.2uF;
C15, C19;603;2;33pF;
C21, C24, C40, C69, C70, C73, C75;603;7;1uF;
C22, C25, C43, C46;603;4;10uF;
C77, C78, C79, C80, C81, C82, C83, C84, C85, C86, C87, C88, C89, C90, C91, C92;603;16;0.01uF;
D1, D2, D3, D39, D4, D40, D41, D42, D43, D44;402;10;LED G;C130722
D10;D_SOD-523;1;1N4148WT;C27748
D11, D14, D17, D20, D23, D26, D29, D32, D35, D38;603;10;LED W;C158100
D12, D13, D15, D16, D18, D19;402;6;LED R;C130719
D21, D22, D24, D25, D27, D28, D7, D8;402;8;LED O;C130720
D30, D31, D33, D34, D36, D37, D5, D6;402;8;LED Y;C130721
D9;SOD3716X135N;1;MBR0520LT3G;C165467
F1;805;1;MF-PSMF075X-2;C116173
FB1, FB2;603;2;BLM18AG102SN1D;C85824
FB3, FB4, FB5, FB6, FB7, FB8, FB9;603;7;BLM18AG601SN1D;C19330
IC1;SOP80P1176X120-54N;1;IS42S16800J-7TL-TR;C2063470
IC2;QFP50P2200X2200X160-144N;1;STM32H723ZGT6;C730146
IC3;SOT95P280X100-5N;1;MP3302DJ-LF-Z;C15035
IC4, IC5;SOT95P285X140-5N;2;AP2112K-3.3TRG1;C51118
IC6;SOT95P285X140-5N;1;AP2112K-1.8TRG1;C176944
IC7;QFN50P500X500X90-33N;1;SGTL5000XNBA3R2;C511764
J1;TYPEC31M17;1;TYPE-C-31-M-17;C283540
J10, J4, J5, J6, J7, J8, J9;SJ13515SMTTR;7;SJ1-3515-SMT-TR;C92633
J2;HIROSE_FH26W-51S-0.3SHW_60_;1;FH26W-51S-0.3SHW_60_;C424656
J3;M208890345;1;M20-8890345;C5242196
L1;NRS5024T4R7MMGJ;1;NRS5024T4R7MMGJ;C2043431
MICRO_SD;TF-01A;1;TF-01A;C91145
R1, R2;603;2;5.1K;
R10, R100, R101, R102, R103, R104, R105, R106, R107, R108, R109, R110, R111, R112, R113, R114, R115, R116, R117, R118, R119, R12, R120, R121, R122, R16, R23, R24, R25, R26, R28, R29, R32, R36, R37, R38, R39, R4, R40, R41, R42, R43, R44, R45, R46, R47, R81, R82, R83, R84, R85, R86, R87, R88, R99;603;55;10K;
R11, R14, R17, R20, R56, R57, R6, R60, R61, R64, R65, R67, R68, R70, R71, R73, R74, R76, R77, R79, R8, R80, R9, R90, R91, R93, R94, R95, R96, R97, R98;603;31;2.2K;
R13, R7;603;2;100K;
R15, R18, R19, R21, R22;603;5;47K;
R27;603;1;10;
R3, R55, R59, R63, R66, R69, R72, R75, R78, R89, R92;603;11;3.3K;
R30, R31, R48;603;3;220;
R33, R34, R35, R50, R51, R52, R54;603;7;0;
R49;603;1;100;
R5;603;1;4.7;
R53;603;1;470;
R58, R62;603;2;47;
S1;SC12PAQR;1;SC12P-AQR;C240300
S2, S3;431481031816;2;431481031816;
SW1, SW10, SW11, SW12, SW13, SW14, SW15, SW16, SW17, SW18, SW19, SW2, SW20, SW21, SW22, SW23, SW24, SW25, SW26, SW27, SW28, SW29, SW3, SW30, SW31, SW32, SW33, SW34, SW35, SW36, SW37, SW38, SW39, SW4, SW40, SW41, SW42, SW5, SW6, SW7, SW8, SW9;SW_PG1350;42;SW_Push;
U1, U2, U3, U4, U5, U6;QFN65P600X600X100-29N-D;6;MCP23017_ML;C629439
U10, U11, U12, U13, U14, U15, U8, U9;PEC12R4017FN0024;8;PEC12R-4017F-N0024;
U7;SMDIP-6_W9.53mm;1;H11L1;C78589
Y1;ABM7;1;ABM7-8MHZ-D2Y-T;C596892

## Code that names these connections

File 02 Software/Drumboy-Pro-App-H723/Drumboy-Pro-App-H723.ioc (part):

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Mcu.Name=STM32H723ZGTx
Mcu.Package=LQFP144
Mcu.UserName=STM32H723ZGTx
PA0.GPIOParameters=GPIO_PuPd,GPIO_Label,GPIO_ModeDefaultEXTI
PA0.GPIO_Label=MX_A_INT
PA0.GPIO_ModeDefaultEXTI=GPIO_MODE_IT_FALLING
PA0.GPIO_PuPd=GPIO_PULLUP
PA0.Signal=GPXTI0
PA1.GPIOParameters=GPIO_PuPd,GPIO_Label,GPIO_ModeDefaultEXTI
PA1.GPIO_Label=MX_B_INT
PA1.GPIO_ModeDefaultEXTI=GPIO_MODE_IT_FALLING
PA1.GPIO_PuPd=GPIO_PULLUP
PA1.Signal=GPXTI1
PA10.GPIOParameters=GPIO_PuPd,GPIO_Label
PA10.GPIO_Label=SYNC_OUT_PULSE
PA10.GPIO_PuPd=GPIO_PULLDOWN
PA10.Signal=GPIO_Output
PA11.GPIOParameters=GPIO_PuPd,GPIO_Label
PA11.GPIO_Label=SYNC_OUT_GND
PA11.GPIO_PuPd=GPIO_NOPULL
PA11.Signal=GPIO_Output
PA12.GPIOParameters=GPIO_Label
PA12.GPIO_Label=SYNC_OUT_GATE
PA12.Signal=GPIO_Output
PA13(JTMS/SWDIO).Mode=Serial_Wire
PA13(JTMS/SWDIO).Signal=DEBUG_JTMS-SWDIO
PA14(JTCK/SWCLK).Mode=Serial_Wire
PA14(JTCK/SWCLK).Signal=DEBUG_JTCK-SWCLK
PA15(JTDI).GPIOParameters=GPIO_PuPd,GPIO_Label
PA15(JTDI).GPIO_Label=SYNC_IN_PULSE
PA15(JTDI).GPIO_PuPd=GPIO_PULLDOWN
PA15(JTDI).Signal=GPXTI15
PA4.GPIOParameters=GPIO_Speed
PA4.GPIO_Speed=GPIO_SPEED_FREQ_LOW
PA4.Mode=Full_Duplex_Master
PA4.Signal=I2S3_WS
PA5.GPIOParameters=GPIO_PuPd,GPIO_Label,GPIO_Mode
PA5.GPIO_Label=ENCO_1B
PA5.GPIO_Mode=GPIO_MODE_INPUT
PA5.GPIO_PuPd=GPIO_PULLUP
PA5.Signal=GPIO_Input
PA6.GPIOParameters=GPIO_PuPd,GPIO_Label
PA6.GPIO_Label=ENCO_2B
PA6.GPIO_PuPd=GPIO_PULLUP
PA6.Signal=GPIO_Input
PA7.GPIOParameters=GPIO_PuPd,GPIO_Label
PA7.GPIO_Label=ENCO_3B
PA7.GPIO_PuPd=GPIO_PULLUP
PA7.Signal=GPIO_Input
PA8.GPIOParameters=GPIO_Speed,GPIO_Pu
PA8.GPIO_Pu=GPIO_PULLUP
PA8.GPIO_Speed=GPIO_SPEED_FREQ_VERY_HIGH
PA8.Mode=I2C
PA8.Signal=I2C3_SCL
PA9.GPIOParameters=GPIO_Label
PA9.GPIO_Label=MIDI_RX
PA9.Mode=Half_duplex(single_wire_mode)
PA9.Signal=USART1_TX
PB0.GPIOParameters=GPIO_Speed,GPIO_PuPd,GPIO_Label
PB0.GPIO_Label=LCD_D0
PB0.GPIO_PuPd=GPIO_PULLUP
PB0.GPIO_Speed=GPIO_SPEED_FREQ_VERY_HIGH
PB0.Signal=GPIO_Output
PB1.GPIOParameters=GPIO_Speed,GPIO_PuPd,GPIO_Label
PB1.GPIO_Label=LCD_D1
PB1.GPIO_PuPd=GPIO_PULLUP
PB1.GPIO_Speed=GPIO_SPEED_FREQ_VERY_HIGH
PB1.Signal=GPIO_Output
PB10.GPIOParameters=GPIO_Speed,GPIO_Label
PB10.GPIO_Label=LCD_D10
PB10.GPIO_Speed=GPIO_SPEED_FREQ_VERY_HIGH
PB10.Signal=GPIO_Output
PB11.GPIOParameters=GPIO_Speed,GPIO_Label
PB11.GPIO_Label=LCD_D11
PB11.GPIO_Speed=GPIO_SPEED_FREQ_VERY_HIGH
PB11.Signal=GPIO_Output
PB12.GPIOParameters=GPIO_Speed,GPIO_Label
PB12.GPIO_Label=LCD_D12
PB12.GPIO_Speed=GPIO_SPEED_FREQ_VERY_HIGH
PB12.Signal=GPIO_Output
PB13.GPIOParameters=GPIO_Speed,GPIO_Label
PB13.GPIO_Label=LCD_D13
PB13.GPIO_Speed=GPIO_SPEED_FREQ_VERY_HIGH
PB13.Signal=GPIO_Output
PB14.GPIOParameters=GPIO_Speed,GPIO_Label
PB14.GPIO_Label=LCD_D14
PB14.GPIO_Speed=GPIO_SPEED_FREQ_VERY_HIGH
PB14.Signal=GPIO_Output
PB15.GPIOParameters=GPIO_Speed,GPIO_Label
PB15.GPIO_Label=LCD_D15
PB15.GPIO_Speed=GPIO_SPEED_FREQ_VERY_HIGH
PB15.Signal=GPIO_Output
PB2.GPIOParameters=GPIO_Speed,GPIO_Label
PB2.GPIO_Label=LCD_D2
PB2.GPIO_Speed=GPIO_SPEED_FREQ_VERY_HIGH
PB2.Signal=GPIO_Output
PB3(JTDO/TRACESWO).GPIOParameters=GPIO_Speed,GPIO_Label
PB3(JTDO/TRACESWO).GPIO_Label=LCD_D3
PB3(JTDO/TRACESWO).GPIO_Speed=GPIO_SPEED_FREQ_VERY_HIGH
PB3(JTDO/TRACESWO).Signal=GPIO_Output
PB4(NJTRST).GPIOParameters=GPIO_Speed,GPIO_Label
PB4(NJTRST).GPIO_Label=LCD_D4
PB4(NJTRST).GPIO_Speed=GPIO_SPEED_FREQ_VERY_HIGH
PB4(NJTRST).Signal=GPIO_Output
PB5.GPIOParameters=GPIO_Speed,GPIO_Label
PB5.GPIO_Label=LCD_D5
PB5.GPIO_Speed=GPIO_SPEED_FREQ_VERY_HIGH
PB5.Signal=GPIO_Output
PB6.GPIOParameters=GPIO_Speed,GPIO_Label
PB6.GPIO_Label=LCD_D6
PB6.GPIO_Speed=GPIO_SPEED_FREQ_VERY_HIGH
PB6.Signal=GPIO_Output
PB7.GPIOParameters=GPIO_Speed,GPIO_Label
PB7.GPIO_Label=LCD_D7
PB7.GPIO_Speed=GPIO_SPEED_FREQ_VERY_HIGH
PB7.Signal=GPIO_Output
PB8.GPIOParameters=GPIO_Speed,GPIO_Label
PB8.GPIO_Label=LCD_D8
PB8.GPIO_Speed=GPIO_SPEED_FREQ_VERY_HIGH
PB8.Signal=GPIO_Output
PB9.GPIOParameters=GPIO_Speed,GPIO_Label
PB9.GPIO_Label=LCD_D9
PB9.GPIO_Speed=GPIO_SPEED_FREQ_VERY_HIGH
PB9.Signal=GPIO_Output
PC0.Signal=FMC_SDNWE
PC1.GPIOParameters=GPIO_Label
PC1.GPIO_Label=LED0
PC1.Signal=GPIO_Output
PC10.GPIOParameters=GPIO_Speed
PC10.GPIO_Speed=GPIO_SPEED_FREQ_LOW
PC10.Mode=Full_Duplex_Master
PC10.Signal=I2S3_CK
PC11.GPIOParameters=GPIO_Speed,GPIO_PuPd
PC11.GPIO_PuPd=GPIO_PULLDOWN
PC11.GPIO_Speed=GPIO_SPEED_FREQ_LOW
PC11.Mode=Full_Duplex_Master
PC11.Signal=I2S3_SDI
PC12.GPIOParameters=GPIO_Speed
PC12.GPIO_Speed=GPIO_SPEED_FREQ_LOW
PC12.Mode=Full_Duplex_Master
PC12.Signal=I2S3_SDO
PC13.GPIOParameters=GPIO_PuPd,GPIO_Label
PC13.GPIO_Label=SDMMC2_DETECT
PC13.GPIO_PuPd=GPIO_PULLUP
PC13.Signal=GPIO_Input
PC14-OSC32_IN.GPIOParameters=GPIO_PuPd,GPIO_Label
PC14-OSC32_IN.GPIO_Label=ENCO_6B
PC14-OSC32_IN.GPIO_PuPd=GPIO_PULLUP
PC14-OSC32_IN.Signal=GPIO_Input
PC15-OSC32_OUT.GPIOParameters=GPIO_PuPd,GPIO_Label
PC15-OSC32_OUT.GPIO_Label=ENCO_7B
PC15-OSC32_OUT.GPIO_PuPd=GPIO_PULLUP
PC15-OSC32_OUT.Signal=GPIO_Input
PC2_C.GPIOParameters=GPIO_Label
PC2_C.GPIO_Label=LED1
PC2_C.Signal=GPIO_Output
PC3_C.GPIOParameters=GPIO_Label
PC3_C.GPIO_Label=LED2
PC3_C.Signal=GPIO_Output
PC4.Mode=SdramChipSelect1_1
PC4.Signal=FMC_SDNE0
PC5.Mode=SdramChipSelect1_1
PC5.Signal=FMC_SDCKE0
PC6.GPIOParameters=GPIO_Label
PC6.GPIO_Label=MIDI_TX
PC6.Mode=Half_duplex(single_wire_mode)
PC6.Signal=USART6_TX
PC7.GPIOParameters=GPIO_Speed
PC7.GPIO_Speed=GPIO_SPEED_FREQ_MEDIUM
PC7.Mode=Master_Clock_Activated
PC7.Signal=I2S3_MCK
PC9.GPIOParameters=GPIO_Speed,GPIO_Pu
PC9.GPIO_Pu=GPIO_PULLUP
PC9.GPIO_Speed=GPIO_SPEED_FREQ_VERY_HIGH
PC9.Mode=I2C
PC9.Signal=I2C3_SDA
PD0.Signal=FMC_D2_DA2
PD1.Signal=FMC_D3_DA3
PD10.Signal=FMC_D15_DA15
PD11.GPIOParameters=GPIO_PuPd,GPIO_Label,GPIO_ModeDefaultEXTI
PD11.GPIO_Label=MX_X_INT
PD11.GPIO_ModeDefaultEXTI=GPIO_MODE_IT_FALLING
PD11.GPIO_PuPd=GPIO_PULLUP
PD11.Signal=GPXTI11
PD12.GPIOParameters=GPIO_Speed,GPIO_Pu
PD12.GPIO_Pu=GPIO_PULLUP
PD12.GPIO_Speed=GPIO_SPEED_FREQ_VERY_HIGH
PD12.Mode=I2C
PD12.Signal=I2C4_SCL
PD13.GPIOParameters=GPIO_Speed,GPIO_Pu
PD13.GPIO_Pu=GPIO_PULLUP
PD13.GPIO_Speed=GPIO_SPEED_FREQ_VERY_HIGH
PD13.Mode=I2C
PD13.Signal=I2C4_SDA
PD14.Signal=FMC_D0_DA0
PD15.Signal=FMC_D1_DA1
PD2.GPIOParameters=GPIO_Speed,GPIO_Label
PD2.GPIO_Label=LCD_CS
PD2.GPIO_Speed=GPIO_SPEED_FREQ_VERY_HIGH
PD2.Signal=GPIO_Output
PD3.GPIOParameters=GPIO_Speed,GPIO_Label
PD3.GPIO_Label=LCD_RD
PD3.GPIO_Speed=GPIO_SPEED_FREQ_VERY_HIGH
PD3.Signal=GPIO_Output
PD4.GPIOParameters=GPIO_Speed,GPIO_Label
PD4.GPIO_Label=LCD_WR
PD4.GPIO_Speed=GPIO_SPEED_FREQ_VERY_HIGH
PD4.Signal=GPIO_Output
PD5.GPIOParameters=GPIO_Speed,GPIO_Label
PD5.GPIO_Label=LCD_RS
PD5.GPIO_Speed=GPIO_SPEED_FREQ_VERY_HIGH
PD5.Signal=GPIO_Output
PD6.Mode=SD_4_bits_Wide_bus
PD6.Signal=SDMMC2_CK
PD7.GPIOParameters=GPIO_PuPd
PD7.GPIO_PuPd=GPIO_NOPULL
PD7.Mode=SD_4_bits_Wide_bus
PD7.Signal=SDMMC2_CMD
PD8.Signal=FMC_D13_DA13
PD9.Signal=FMC_D14_DA14
PE0.Signal=FMC_NBL0
PE1.Signal=FMC_NBL1
PE10.Signal=FMC_D7_DA7
PE11.Signal=FMC_D8_DA8
PE12.Signal=FMC_D9_DA9
PE13.Signal=FMC_D10_DA10
PE14.Signal=FMC_D11_DA11
PE15.Signal=FMC_D12_DA12
PE2.GPIOParameters=GPIO_PuPd,GPIO_Label,GPIO_ModeDefaultEXTI
PE2.GPIO_Label=ENCO_0A
PE2.GPIO_ModeDefaultEXTI=GPIO_MODE_IT_RISING_FALLING
PE2.GPIO_PuPd=GPIO_PULLUP
PE2.Signal=GPXTI2
PE3.GPIOParameters=GPIO_PuPd,GPIO_Label,GPIO_ModeDefaultEXTI
PE3.GPIO_Label=ENCO_1A
PE3.GPIO_ModeDefaultEXTI=GPIO_MODE_IT_RISING_FALLING
PE3.GPIO_PuPd=GPIO_PULLUP
PE3.Signal=GPXTI3
PE4.GPIOParameters=GPIO_PuPd,GPIO_Label,GPIO_ModeDefaultEXTI
PE4.GPIO_Label=ENCO_2A
PE4.GPIO_ModeDefaultEXTI=GPIO_MODE_IT_RISING_FALLING
PE4.GPIO_PuPd=GPIO_PULLUP
PE4.Signal=GPXTI4
PE5.GPIOParameters=GPIO_PuPd,GPIO_Label,GPIO_ModeDefaultEXTI
PE5.GPIO_Label=ENCO_3A
PE5.GPIO_ModeDefaultEXTI=GPIO_MODE_IT_RISING_FALLING
PE5.GPIO_PuPd=GPIO_PULLUP
PE5.Signal=GPXTI5
PE6.GPIOParameters=GPIO_PuPd,GPIO_Label
PE6.GPIO_Label=ENCO_0B
PE6.GPIO_PuPd=GPIO_PULLUP
PE6.Signal=GPIO_Input
PE7.Signal=FMC_D4_DA4
PE8.Signal=FMC_D5_DA5
PE9.Signal=FMC_D6_DA6
PF0.Signal=FMC_A0
PF1.Signal=FMC_A1
PF10.GPIOParameters=GPIO_PuPd,GPIO_Label,GPIO_ModeDefaultEXTI
PF10.GPIO_Label=BUTTON
PF10.GPIO_ModeDefaultEXTI=GPIO_MODE_IT_FALLING
PF10.GPIO_PuPd=GPIO_PULLUP
PF10.Signal=GPXTI10
PF11.Signal=FMC_SDNRAS
PF12.Signal=FMC_A6
PF13.Signal=FMC_A7
PF14.Signal=FMC_A8
PF15.Signal=FMC_A9
PF2.Signal=FMC_A2
PF3.Signal=FMC_A3
PF4.Signal=FMC_A4
PF5.Signal=FMC_A5
PF6.GPIOParameters=GPIO_PuPd,GPIO_Label
PF6.GPIO_Label=SYNC_IN_GATE
PF6.GPIO_PuPd=GPIO_PULLDOWN
PF6.Signal=GPIO_Input
PF7.GPIOParameters=GPIO_Label
PF7.GPIO_Label=SYNC_IN_GND
PF7.Signal=GPIO_Output
PF8.GPIOParameters=GPIO_PuPd,GPIO_Label,GPIO_ModeDefaultEXTI
PF8.GPIO_Label=ENCO_6A
PF8.GPIO_ModeDefaultEXTI=GPIO_MODE_IT_RISING_FALLING
PF8.GPIO_PuPd=GPIO_PULLUP
PF8.Signal=GPXTI8
PF9.GPIOParameters=GPIO_PuPd,GPIO_Label,GPIO_ModeDefaultEXTI
PF9.GPIO_Label=ENCO_7A
PF9.GPIO_ModeDefaultEXTI=GPIO_MODE_IT_RISING_FALLING
PF9.GPIO_PuPd=GPIO_PULLUP
PF9.Signal=GPXTI9
PG0.Signal=FMC_A10
PG1.Signal=FMC_A11
PG10.Mode=SD_4_bits_Wide_bus
PG10.Signal=SDMMC2_D1
PG11.Mode=SD_4_bits_Wide_bus
PG11.Signal=SDMMC2_D2

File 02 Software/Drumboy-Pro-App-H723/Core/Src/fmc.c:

/* USER CODE BEGIN Header */
/**
  ******************************************************************************
  * File Name          : FMC.c
  * Description        : This file provides code for the configuration
  *                      of the FMC peripheral.
  ******************************************************************************
  * @attention
  *
  * Copyright (c) 2025 STMicroelectronics.
  * All rights reserved.
  *
  * This software is licensed under terms that can be found in the LICENSE file
  * in the root directory of this software component.
  * If no LICENSE file comes with this software, it is provided AS-IS.
  *
  ******************************************************************************
  */
/* USER CODE END Header */

/* Includes ------------------------------------------------------------------*/
#include "fmc.h"

/* USER CODE BEGIN 0 */

/* USER CODE END 0 */

SDRAM_HandleTypeDef hsdram1;

/* FMC initialization function */
void MX_FMC_Init(void)
{
  /* USER CODE BEGIN FMC_Init 0 */

  /* USER CODE END FMC_Init 0 */

  FMC_SDRAM_TimingTypeDef SdramTiming = {0};

  /* USER CODE BEGIN FMC_Init 1 */

  /* USER CODE END FMC_Init 1 */

  /** Perform the SDRAM1 memory initialization sequence
  */
  hsdram1.Instance = FMC_SDRAM_DEVICE;
  /* hsdram1.Init */
  hsdram1.Init.SDBank = FMC_SDRAM_BANK1;
  hsdram1.Init.ColumnBitsNumber = FMC_SDRAM_COLUMN_BITS_NUM_9;
  hsdram1.Init.RowBitsNumber = FMC_SDRAM_ROW_BITS_NUM_12;
  hsdram1.Init.MemoryDataWidth = FMC_SDRAM_MEM_BUS_WIDTH_16;
  hsdram1.Init.InternalBankNumber = FMC_SDRAM_INTERN_BANKS_NUM_4;
  hsdram1.Init.CASLatency = FMC_SDRAM_CAS_LATENCY_2;
  hsdram1.Init.WriteProtection = FMC_SDRAM_WRITE_PROTECTION_DISABLE;
  hsdram1.Init.SDClockPeriod = FMC_SDRAM_CLOCK_PERIOD_2;
  hsdram1.Init.ReadBurst = FMC_SDRAM_RBURST_ENABLE;
  hsdram1.Init.ReadPipeDelay = FMC_SDRAM_RPIPE_DELAY_2;
  /* SdramTiming */
  SdramTiming.LoadToActiveDelay = 2;
  SdramTiming.ExitSelfRefreshDelay = 9;
  SdramTiming.SelfRefreshTime = 5;
  SdramTiming.RowCycleDelay = 8;
  SdramTiming.WriteRecoveryTime = 4;
  SdramTiming.RPDelay = 2;
  SdramTiming.RCDDelay = 2;

  if (HAL_SDRAM_Init(&hsdram1, &SdramTiming) != HAL_OK)
  {
    Error_Handler( );
  }

  /* USER CODE BEGIN FMC_Init 2 */

  /* USER CODE END FMC_Init 2 */
}

static uint32_t FMC_Initialized = 0;

static void HAL_FMC_MspInit(void){
  /* USER CODE BEGIN FMC_MspInit 0 */

  /* USER CODE END FMC_MspInit 0 */
  GPIO_InitTypeDef GPIO_InitStruct = {0};
  if (FMC_Initialized) {
    return;
  }
  FMC_Initialized = 1;

  /* Peripheral clock enable */
  __HAL_RCC_FMC_CLK_ENABLE();

  /** FMC GPIO Configuration
  PF0   ------> FMC_A0
  PF1   ------> FMC_A1
  PF2   ------> FMC_A2
  PF3   ------> FMC_A3
  PF4   ------> FMC_A4
  PF5   ------> FMC_A5
  PC0   ------> FMC_SDNWE
  PC4   ------> FMC_SDNE0
  PC5   ------> FMC_SDCKE0
  PF11   ------> FMC_SDNRAS
  PF12   ------> FMC_A6
  PF13   ------> FMC_A7
  PF14   ------> FMC_A8
  PF15   ------> FMC_A9
  PG0   ------> FMC_A10
  PG1   ------> FMC_A11
  PE7   ------> FMC_D4
  PE8   ------> FMC_D5
  PE9   ------> FMC_D6
  PE10   ------> FMC_D7
  PE11   ------> FMC_D8
  PE12   ------> FMC_D9
  PE13   ------> FMC_D10
  PE14   ------> FMC_D11
  PE15   ------> FMC_D12
  PD8   ------> FMC_D13
  PD9   ------> FMC_D14
  PD10   ------> FMC_D15
  PD14   ------> FMC_D0
  PD15   ------> FMC_D1
  PG4   ------> FMC_BA0
  PG5   ------> FMC_BA1
  PG8   ------> FMC_SDCLK
  PD0   ------> FMC_D2
  PD1   ------> FMC_D3
  PG15   ------> FMC_SDNCAS
  PE0   ------> FMC_NBL0
  PE1   ------> FMC_NBL1
  */
  /* GPIO_InitStruct */
  GPIO_InitStruct.Pin = GPIO_PIN_0|GPIO_PIN_1|GPIO_PIN_2|GPIO_PIN_3
                          |GPIO_PIN_4|GPIO_PIN_5|GPIO_PIN_11|GPIO_PIN_12
                          |GPIO_PIN_13|GPIO_PIN_14|GPIO_PIN_15;
  GPIO_InitStruct.Mode = GPIO_MODE_AF_PP;
  GPIO_InitStruct.Pull = GPIO_NOPULL;
  GPIO_InitStruct.Speed = GPIO_SPEED_FREQ_VERY_HIGH;
  GPIO_InitStruct.Alternate = GPIO_AF12_FMC;

  HAL_GPIO_Init(GPIOF, &GPIO_InitStruct);

  /* GPIO_InitStruct */
  GPIO_InitStruct.Pin = GPIO_PIN_0|GPIO_PIN_4|GPIO_PIN_5;
  GPIO_InitStruct.Mode = GPIO_MODE_AF_PP;
  GPIO_InitStruct.Pull = GPIO_NOPULL;
  GPIO_InitStruct.Speed = GPIO_SPEED_FREQ_VERY_HIGH;
  GPIO_InitStruct.Alternate = GPIO_AF12_FMC;

  HAL_GPIO_Init(GPIOC, &GPIO_InitStruct);

  /* GPIO_InitStruct */
  GPIO_InitStruct.Pin = GPIO_PIN_0|GPIO_PIN_1|GPIO_PIN_4|GPIO_PIN_5
                          |GPIO_PIN_8|GPIO_PIN_15;
  GPIO_InitStruct.Mode = GPIO_MODE_AF_PP;
  GPIO_InitStruct.Pull = GPIO_NOPULL;
  GPIO_InitStruct.Speed = GPIO_SPEED_FREQ_VERY_HIGH;
  GPIO_InitStruct.Alternate = GPIO_AF12_FMC;

  HAL_GPIO_Init(GPIOG, &GPIO_InitStruct);

  /* GPIO_InitStruct */
  GPIO_InitStruct.Pin = GPIO_PIN_7|GPIO_PIN_8|GPIO_PIN_9|GPIO_PIN_10
                          |GPIO_PIN_11|GPIO_PIN_12|GPIO_PIN_13|GPIO_PIN_14
                          |GPIO_PIN_15|GPIO_PIN_0|GPIO_PIN_1;
  GPIO_InitStruct.Mode = GPIO_MODE_AF_PP;
  GPIO_InitStruct.Pull = GPIO_NOPULL;
  GPIO_InitStruct.Speed = GPIO_SPEED_FREQ_VERY_HIGH;
  GPIO_InitStruct.Alternate = GPIO_AF12_FMC;

  HAL_GPIO_Init(GPIOE, &GPIO_InitStruct);

  /* GPIO_InitStruct */
  GPIO_InitStruct.Pin = GPIO_PIN_8|GPIO_PIN_9|GPIO_PIN_10|GPIO_PIN_14
                          |GPIO_PIN_15|GPIO_PIN_0|GPIO_PIN_1;
  GPIO_InitStruct.Mode = GPIO_MODE_AF_PP;
  GPIO_InitStruct.Pull = GPIO_NOPULL;
  GPIO_InitStruct.Speed = GPIO_SPEED_FREQ_VERY_HIGH;
  GPIO_InitStruct.Alternate = GPIO_AF12_FMC;

  HAL_GPIO_Init(GPIOD, &GPIO_InitStruct);

  /* Peripheral interrupt init */
  HAL_NVIC_SetPriority(FMC_IRQn, 0, 2);
  HAL_NVIC_EnableIRQ(FMC_IRQn);
  /* USER CODE BEGIN FMC_MspInit 1 */

  /* USER CODE END FMC_MspInit 1 */
}

void HAL_SDRAM_MspInit(SDRAM_HandleTypeDef* sdramHandle){
  /* USER CODE BEGIN SDRAM_MspInit 0 */

  /* USER CODE END SDRAM_MspInit 0 */
  HAL_FMC_MspInit();
  /* USER CODE BEGIN SDRAM_MspInit 1 */

  /* USER CODE END SDRAM_MspInit 1 */
}

static uint32_t FMC_DeInitialized = 0;

static void HAL_FMC_MspDeInit(void){
  /* USER CODE BEGIN FMC_MspDeInit 0 */

  /* USER CODE END FMC_MspDeInit 0 */
  if (FMC_DeInitialized) {
    return;
  }
  FMC_DeInitialized = 1;
  /* Peripheral clock enable */
  __HAL_RCC_FMC_CLK_DISABLE();

  /** FMC GPIO Configuration
  PF0   ------> FMC_A0
  PF1   ------> FMC_A1
  PF2   ------> FMC_A2
  PF3   ------> FMC_A3
  PF4   ------> FMC_A4
  PF5   ------> FMC_A5
  PC0   ------> FMC_SDNWE
  PC4   ------> FMC_SDNE0
  PC5   ------> FMC_SDCKE0
  PF11   ------> FMC_SDNRAS
  PF12   ------> FMC_A6
  PF13   ------> FMC_A7
  PF14   ------> FMC_A8
  PF15   ------> FMC_A9
  PG0   ------> FMC_A10
  PG1   ------> FMC_A11
  PE7   ------> FMC_D4
  PE8   ------> FMC_D5
  PE9   ------> FMC_D6
  PE10   ------> FMC_D7
  PE11   ------> FMC_D8
  PE12   ------> FMC_D9
  PE13   ------> FMC_D10
  PE14   ------> FMC_D11
  PE15   ------> FMC_D12
  PD8   ------> FMC_D13
  PD9   ------> FMC_D14
  PD10   ------> FMC_D15
  PD14   ------> FMC_D0
  PD15   ------> FMC_D1
  PG4   ------> FMC_BA0
  PG5   ------> FMC_BA1
  PG8   ------> FMC_SDCLK
  PD0   ------> FMC_D2
  PD1   ------> FMC_D3
  PG15   ------> FMC_SDNCAS
  PE0   ------> FMC_NBL0
  PE1   ------> FMC_NBL1
  */

  HAL_GPIO_DeInit(GPIOF, GPIO_PIN_0|GPIO_PIN_1|GPIO_PIN_2|GPIO_PIN_3
                          |GPIO_PIN_4|GPIO_PIN_5|GPIO_PIN_11|GPIO_PIN_12
                          |GPIO_PIN_13|GPIO_PIN_14|GPIO_PIN_15);

  HAL_GPIO_DeInit(GPIOC, GPIO_PIN_0|GPIO_PIN_4|GPIO_PIN_5);

  HAL_GPIO_DeInit(GPIOG, GPIO_PIN_0|GPIO_PIN_1|GPIO_PIN_4|GPIO_PIN_5
                          |GPIO_PIN_8|GPIO_PIN_15);

  HAL_GPIO_DeInit(GPIOE, GPIO_PIN_7|GPIO_PIN_8|GPIO_PIN_9|GPIO_PIN_10
                          |GPIO_PIN_11|GPIO_PIN_12|GPIO_PIN_13|GPIO_PIN_14
                          |GPIO_PIN_15|GPIO_PIN_0|GPIO_PIN_1);

  HAL_GPIO_DeInit(GPIOD, GPIO_PIN_8|GPIO_PIN_9|GPIO_PIN_10|GPIO_PIN_14
                          |GPIO_PIN_15|GPIO_PIN_0|GPIO_PIN_1);

  /* Peripheral interrupt DeInit */
  HAL_NVIC_DisableIRQ(FMC_IRQn);
  /* USER CODE BEGIN FMC_MspDeInit 1 */

  /* USER CODE END FMC_MspDeInit 1 */
}

void HAL_SDRAM_MspDeInit(SDRAM_HandleTypeDef* sdramHandle){
  /* USER CODE BEGIN SDRAM_MspDeInit 0 */

  /* USER CODE END SDRAM_MspDeInit 0 */
  HAL_FMC_MspDeInit();
  /* USER CODE BEGIN SDRAM_MspDeInit 1 */

  /* USER CODE END SDRAM_MspDeInit 1 */
}
/**
  * @}
  */

/**
  * @}
  */
